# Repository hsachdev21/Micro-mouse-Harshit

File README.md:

# Micro-mouse-Harshit
All the assignment submission for micro mouse project and all the other things.

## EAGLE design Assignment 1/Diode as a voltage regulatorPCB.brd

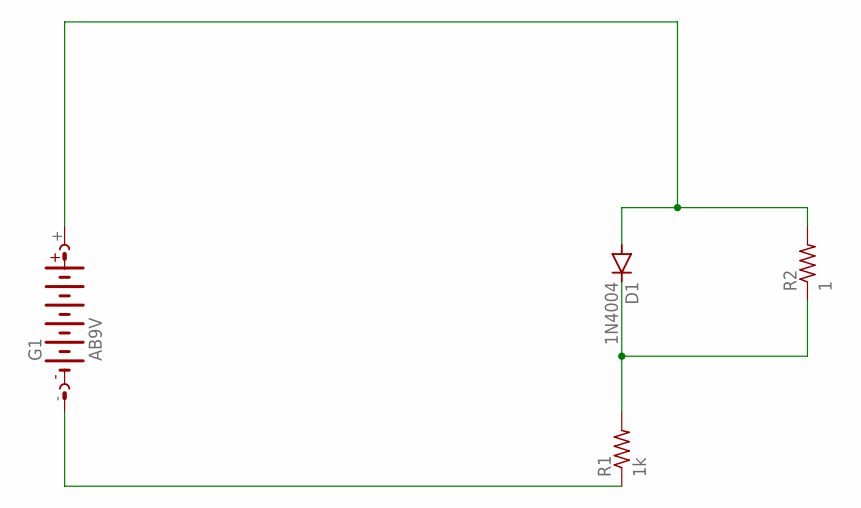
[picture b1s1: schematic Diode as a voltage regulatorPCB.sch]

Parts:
D1: 1N4004; DO41-10
G1: AB9V
R1: 1k; R0805
R2: 1; R0805

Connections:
unnamed: G1.-, R1.1
unnamed: D1.C, R1.2, R2.1
unnamed: D1.A, G1.+, R2.2

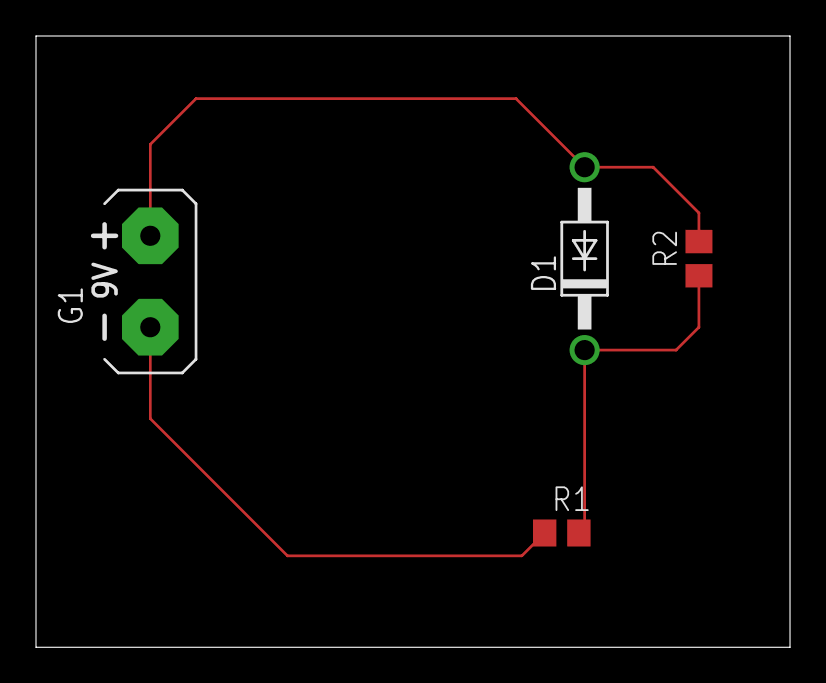
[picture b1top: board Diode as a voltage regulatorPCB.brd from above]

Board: 2 copper layers, 41.9 x 34.0 mm, 4 parts (0 on the bottom side), 3 nets.

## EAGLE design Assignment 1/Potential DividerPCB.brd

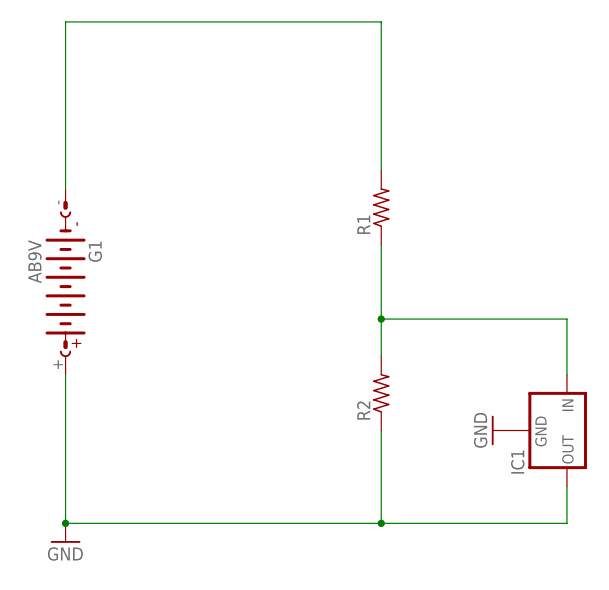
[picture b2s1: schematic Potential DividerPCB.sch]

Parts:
G1: AB9V
IC1: 78LXX
R1, R2: R-US_R0805; R0805

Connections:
GND: G1.+, IC1.GND, IC1.OUT, R2.1
unnamed: G1.-, R1.2
unnamed: IC1.IN, R1.1, R2.2

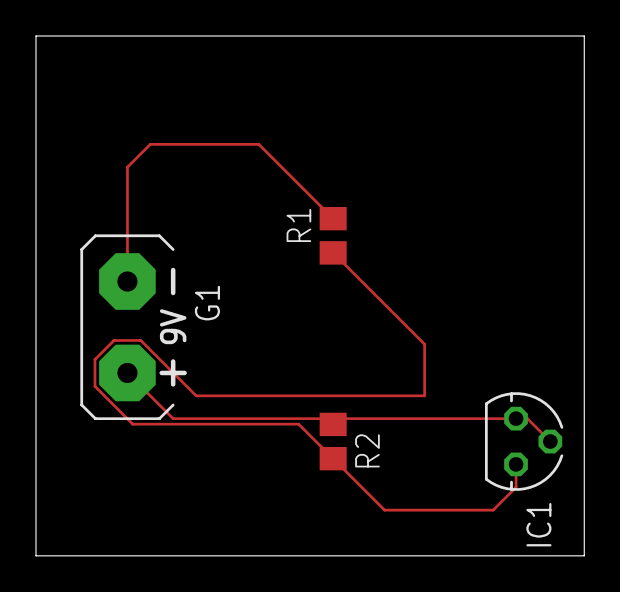
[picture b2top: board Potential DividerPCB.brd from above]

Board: 2 copper layers, 30.5 x 28.9 mm, 4 parts (0 on the bottom side), 3 nets.

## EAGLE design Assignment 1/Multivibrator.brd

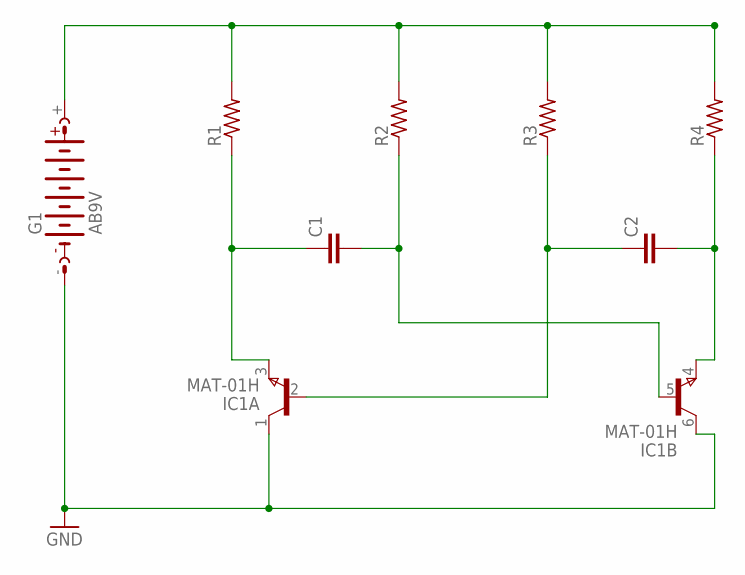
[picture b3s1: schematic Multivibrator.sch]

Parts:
C1, C2: C2,5-3; C2.5-3
G1: AB9V
IC1: MAT-01H; TO78
R1, R2, R3, R4: R-US_R0805; R0805

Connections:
GND: G1.-, IC1.1 (C), IC1.6 (C)
unnamed: G1.+, R1.2, R2.2, R3.2, R4.2
unnamed: C1.1, IC1.3 (E), R1.1
unnamed: C1.2, IC1.5 (B), R2.1
unnamed: C2.1, IC1.2 (B), R3.1
unnamed: C2.2, IC1.4 (E), R4.1

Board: 2 copper layers, 8 parts (0 on the bottom side), 6 nets, no tracks yet.

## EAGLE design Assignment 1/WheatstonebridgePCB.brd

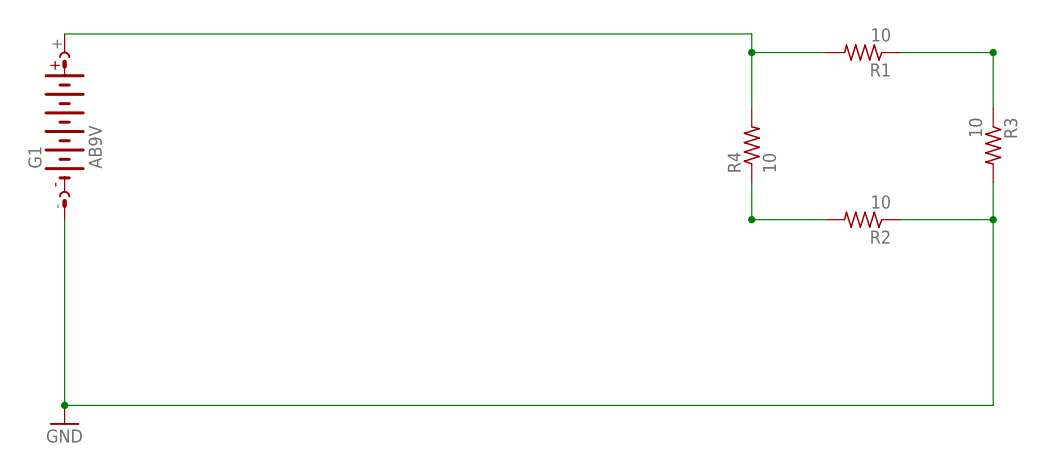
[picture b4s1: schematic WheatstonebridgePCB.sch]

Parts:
G1: AB9V
R1, R2, R3, R4: 10; R0805

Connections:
GND: G1.-, R2.1, R3.2
unnamed: G1.+, R1.2, R4.2
unnamed: R1.1, R3.1
unnamed: R2.2, R4.1

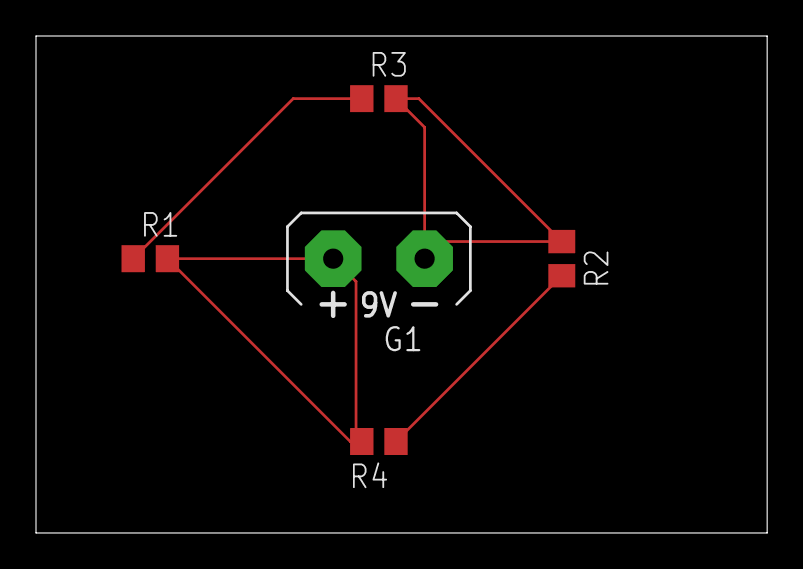
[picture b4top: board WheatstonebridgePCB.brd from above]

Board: 2 copper layers, 40.6 x 27.6 mm, 5 parts (0 on the bottom side), 4 nets.

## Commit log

2022-07-18 Assignment 1 PCB designing uploaded.
